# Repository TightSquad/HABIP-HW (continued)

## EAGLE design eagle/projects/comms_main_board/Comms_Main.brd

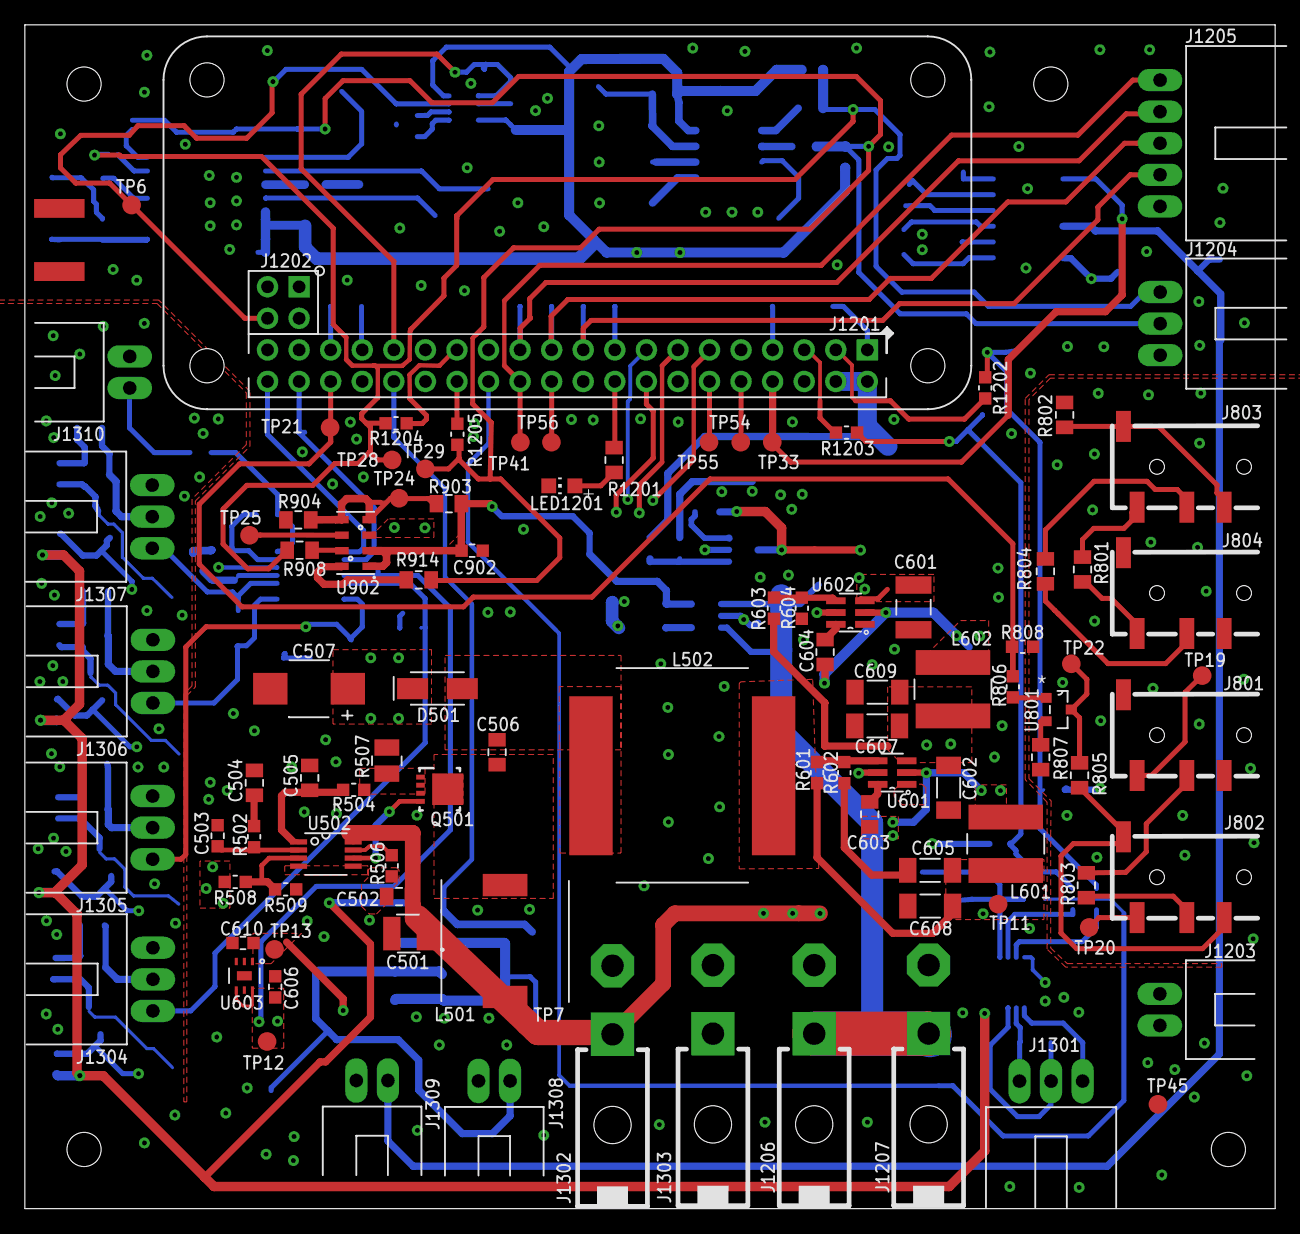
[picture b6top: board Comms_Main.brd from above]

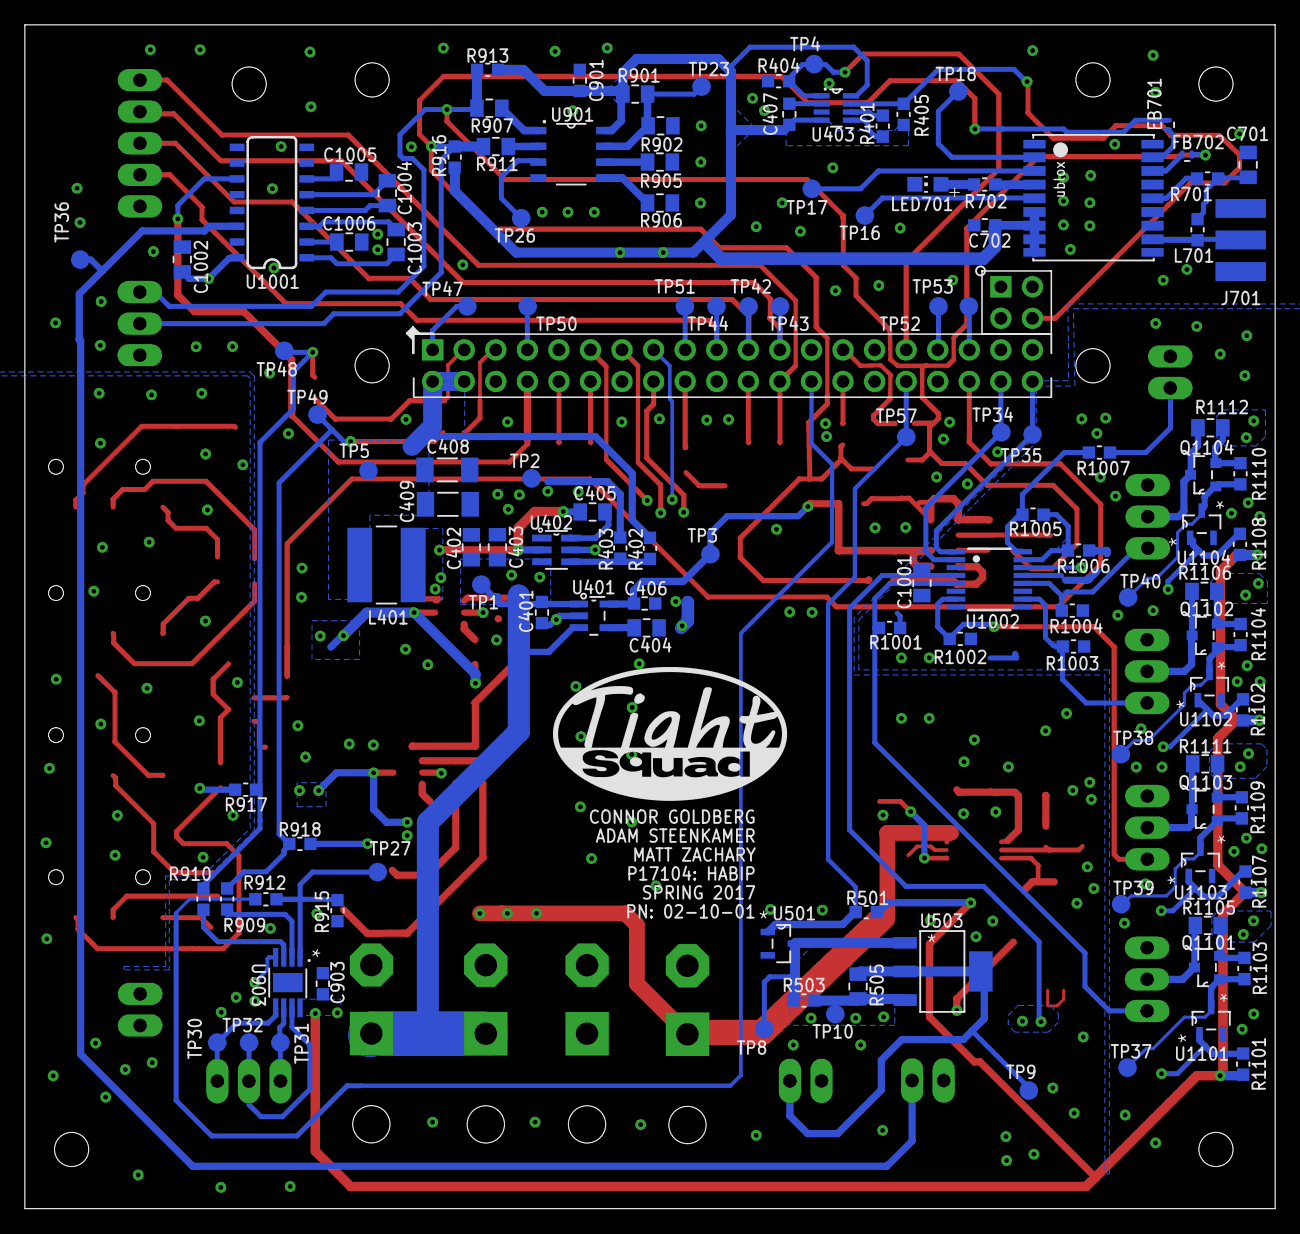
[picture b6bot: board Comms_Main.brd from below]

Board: 4 copper layers, 100.6 x 95.2 mm, 297 parts (122 on the bottom side), 126 nets.

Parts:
C401, C606, C610: 1uF; C0603
C402, C403: 10uF; C0805
C404, C701: 10nF; C0805
C405, C502, C504, C603, C604, C1001, C1002, C1003, C1004, C1005, C1006: 100nF; C0805
C406: 4.7uF; C0603
C407, C702, C901, C902, C903: 100nF; C0603
C408, C409, C602, C605, C607, C608, C609: 22uF; C1206
C501: 8.2 uF; C1411
C503: 2.4nF; C0603
C505: 620pF; C0805
C506: 4.7uF; C0805
C507: 47uF; C2917
C601: 22uF; C1210
D501: CDBA340-HF; DO-214AC
FB701, FB702: BLM15HD102SN1D; FB0402
H1201, H1202, H1203, H1204: MOUNT-HOLE_2.75; 2,75_HOLE_RASPI
IMAGE101: SQUAD_LOGO
J701: WRL-00593; SMA-EDGE
J801, J802, J803, J804: PRT-12639; AUDIO-JACK-TRRS-SMD
J1201: RECEPTACLE-2x20-254MM; HEADER-2X20-254MM
J1202: RECEPTACLE-2x2-254MM; HEADER-2X2-254MM
J1203, J1308, J1309, J1310: MOL-SL-2-RA; MOLSL-2-RA
J1204, J1301, J1304, J1305, J1306, J1307: MOL-SL-3-RA; MOLSL-3-RA
J1205: MOL-SL-5-RA; MOLSL-5-RA
J1206, J1207, J1302, J1303: MOL-MINIJR-2P-RA; 39-30-?02?
L401, L602: 4.7uH; SRN6045
L501: 10uH; SRU1048
L502: 68uH; HCMA1707
L601: 3.3uH; SRN6045
L701: 27nH; L0603
LED701, LED1201: LTST-C170CKT; CHIP-LED0805
OFFBOARD1, OFFBOARD7, OFFBOARD11, OFFBOARD30, OFFBOARD34, OFFBOARD38: 50-57-9403; MOLSL-OFFBOARD
OFFBOARD2, OFFBOARD4, OFFBOARD8, OFFBOARD10, OFFBOARD12, OFFBOARD14, OFFBOARD16, OFFBOARD17, OFFBOARD18, OFFBOARD19, OFFBOARD20, OFFBOARD21, OFFBOARD22, OFFBOARD23, OFFBOARD24, OFFBOARD25, OFFBOARD26, OFFBOARD27, OFFBOARD28, OFFBOARD29, OFFBOARD31, OFFBOARD32, OFFBOARD33, OFFBOARD35, OFFBOARD36, OFFBOARD37, OFFBOARD39, OFFBOARD40, OFFBOARD41, OFFBOARD43, OFFBOARD44: 0016020087; MOLSL-OFFBOARD
OFFBOARD3: 0050579405; MOLSL-OFFBOARD
OFFBOARD5: 67996-104HLF; MOLSL-OFFBOARD
OFFBOARD6: PRPC020DAAN-RC; MOLSL-OFFBOARD
OFFBOARD9, OFFBOARD13, OFFBOARD15, OFFBOARD42, OFFBOARD48: 50-57-9402; MOLSL-OFFBOARD
OFFBOARD45: 0701070001; MOLSL-OFFBOARD
OFFBOARD46, OFFBOARD47: 0016020115; MOLSL-OFFBOARD
OFFBOARD49, OFFBOARD52, OFFBOARD55, OFFBOARD56, OFFBOARD64, OFFBOARD65: 0039013022; MOLSL-OFFBOARD
OFFBOARD50, OFFBOARD51, OFFBOARD53, OFFBOARD54, OFFBOARD57, OFFBOARD58, OFFBOARD59, OFFBOARD60, OFFBOARD66, OFFBOARD67, OFFBOARD68, OFFBOARD69: 0039000073; MOLSL-OFFBOARD
OFFBOARD61, OFFBOARD70: 0039013023; MOLSL-OFFBOARD
OFFBOARD62, OFFBOARD63, OFFBOARD71, OFFBOARD72: 0039000075; MOLSL-OFFBOARD
OUTLINE1201: RASPI-ZERO-4STANDOFFS-0CAM; RASPI_ZERO_4STANDOFFS
Q501: CSD17579Q3A; DNH0008A
Q1101, Q1102, Q1103, Q1104: NTR4101PT1G; SOT103P240X110-3N
R401, R909, R910, R912, R915, R1005, R1006: 0; R0603
R402, R603: 56.2k; R0603
R403, R404, R405, R501, R503, R509, R602, R604, R1101, R1102, R1103, R1104, R1107, R1108, R1109, R1110: 10k; R0603
R502: 1.15k; R0603
R504: 100; R0603
R505, R801, R802, R803, R804, R805, R807, R901, R902, R903, R904, R905, R906, R907, R908, R911, R914, R1105, R1106, R1111, R1112: 0.0; R0805
R506: 30.1k; R0603
R507: 0.016; R1206
R508: 84.5k; R0603
R601: 33.2k; R0603
R701: 10; R0603
R702: 390; R0603
R806, R808: 1k; R0603
R913, R916, R917, R918: 4.7k; R0603
R1001, R1002, R1003, R1004, R1007: 75; R0603
R1201: 150; R0805
R1202, R1203, R1204, R1205: 23.2; R0603
TP1, TP2, TP3, TP4, TP5, TP6, TP7, TP8, TP9, TP10, TP11, TP12, TP13, TP16, TP17, TP18, TP19, TP20, TP21, TP22, TP23, TP24, TP25, TP26, TP27, TP28, TP29, TP30, TP31, TP32, TP33, TP34, TP35, TP36, TP37, TP38, TP39, TP40, TP41, TP42, TP43, TP44, TP45, TP47, TP48, TP49, TP50, TP51, TP52, TP53, TP54, TP55, TP56, TP57: TPTP15R; TP15R
U401: LP2985-33DBVR; DBV5
U402, U601, U602: TPS562209DDCT; DDC0006A
U403: MAX6371; SOT23P130X045-8N
U501, U1101, U1102, U1103, U1104: 2N7002P,215; SOT95P230X110-3N
U502: LM3488MMX/NOPB; MUA08A
U503: NDT2955; SOT230P700X180-4N
U603: LP5900SD-3.3/NOPB; 6WDFN
U701: MAX-M8Q; UBLOX_MAX
U801: MMBT3904-HF; SOT103P240X110-3N
U901: PCT2075D,118; SOIC127P130X0600-8N
U902: MS560702BA03-50; SMD125P110X060-8N
U903: MCP4541-103E/MS; SOP65P490X110-8N
U1001: MAX3232CSE+; SO016
U1002: MAX4311; QSOP16

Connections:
3P3V_DIG_POT: C605.1, C608.1, C903.1, L601.2, R501.2, R601.2, R917.2, R918.2, R1101.2, R1102.2, R1107.2, R1108.2, TP11.TP, U903.8
3P3V_RS232: C610.1, C1002.1, TP13.TP, U603.1, U1001.16
3P3V_SENSORS: C406.1, C407.1, C702.1, C901.2, C902.2, R401.1, R405.2, R901.2, R903.2, R913.2, R916.2, TP3.TP, U401.5, U403.4, U403.5, U403.8, U701.6_V_BCKP, U701.7_VCC_IO, U701.8_VCC, U701.9_V_RESET, U901.8, U902.1, U902.2
5V_BOARD: C602.1, C606.1, C607.1, C609.1, C1001.1, L602.2, Q1101.2, Q1102.2, Q1103.2, Q1104.2, R603.2, R1103.2, R1104.2, R1105.2, R1106.2, R1109.2, R1110.2, R1111.2, R1112.2, TP12.TP, U601.3, U601.5, U603.4, U603.6, U1002.4, U1002.14
5V_BUCK_SW: C604.2, L602.1, U602.2
5V_BUCK_VBST: C604.1, U602.6
5V_BUCK_VFB: R603.1, R604.2, U602.4
5V_CAM0: J1304.2, Q1101.3, R1105.1
5V_CAM1: J1305.2, Q1103.3, R1111.1
5V_CAM2: J1306.2, Q1102.3, R1106.1
5V_CAM3: J1307.2, Q1104.3, R1112.1
5V_PI: C408.1, C409.1, J1201.2, J1201.4, L401.2, R402.2, TP5.TP
7P4V_IN: C401.1, C402.1, C403.1, J1206.1, J1207.1, TP1.TP, U401.1, U401.3, U402.3, U402.5
11P1V_IN: C501.1, C502.1, C601.1, J1302.1, L501.1, TP7.TP, U502.8, U602.3, U602.5
12V_BOARD: C507.1, D501.C, J1303.1, R503.2, R505.2, R508.2, TP10.TP, U503.3
12V_PI_CONTROLLED: J1308.1, R505.1, TP9.TP, U503.2, U503.4
12V_PMOS_G: R503.1, TP8.TP, U501.3, U503.1
BUCK_POT_SW: C603.2, L601.1, U601.2
BUCK_POT_VBST: C603.1, U601.6
BUCK_POT_VFB: R601.1, R602.2, U601.4
CAM0_P_G: Q1101.1, R1103.1, TP37.TP, U1101.3
CAM1_P_G: Q1103.1, R1109.1, TP39.TP, U1103.3
CAM2_P_G: Q1102.1, R1104.1, TP38.TP, U1102.3
CAM3_P_G: Q1104.1, R1110.1, TP40.TP, U1104.3
DCDC_STEPUP_COMP: C503.1, R502.2, U502.2
DCDC_STEPUP_DR: Q501.4, U502.6
DCDC_STEPUP_FB: R508.1, R509.2, U502.3
DCDC_STEPUP_ISENSE: C505.1, R504.1, U502.1
DCDC_STEPUP_ISENSE_RES: Q501.1, Q501.2, Q501.3, R504.2, R507.2
DCDC_STEPUP_OUT: C506.1, L501.2, Q501.5, Q501.6, Q501.7, Q501.8, Q501.9, Q501.V
DCDC_STEPUP_PRE_DIODE: C506.2, D501.A, L502.1
DCDC_STEPUP_RC_COMP: C504.1, R502.1
DCDC_STEPUP_SD: R506.2, U502.7
GND: C401.2, C402.2, C403.2, C404.2, C406.2, C407.2, C408.2, C409.2, C501.2, C502.2, C503.2, C504.2, C505.2, C507.2, C601.2, C602.2, C605.2, C606.2, C607.2, C608.2, C609.2, C610.2, C701.2, C702.2, C901.1, C902.1, C903.2, C1001.2, C1002.2, C1005.2, C1006.2, J701.GND@0, J701.GND@1, J701.GND@2, J701.GND@3, J801.EARTH, J801.RING2, J804.EARTH, J804.RING2, J1201.6, J1201.9, J1201.14, J1201.20, J1201.25, J1201.30, J1201.34, J1201.39, J1202.2, J1203.1, J1203.2, J1204.3, J1205.5, J1206.2, J1207.2, J1302.2, J1303.2, J1304.3, J1305.3, J1306.3, J1307.3, J1308.2, J1309.2, J1310.2, L502.2, LED701.C, LED1201.C, R403.1, R404.1, R506.1, R507.1, R509.1, R602.1, R604.1, R802.1, R807.2, R808.2, R902.1, R904.1, R905.1, R906.1, R915.1, R1001.1, R1002.1, R1003.1, R1004.1, R1006.1, TP2.TP, TP45.TP, U401.2, U402.1, U403.2, U501.2, U502.4, U502.5, U601.1, U602.1, U603.3, U603.7, U701.1_GND, U701.10_GND, U701.12_GND, U901.4, U902.3, U903.4, U1001.8, U1001.10, U1001.13, U1001.15, U1002.13, U1101.2, U1102.2, U1103.2, U1104.2
GPIO_MUX_ADDR0: J1201.38, TP34.TP, U1002.2
GPIO_MUX_ADDR1: J1201.40, TP35.TP, U1002.1
GPIO_POT_HVC: J1201.26, R912.1
GPIO_PTT: J1201.36, R806.1, R808.1, TP21.TP
GPS_ANTENNA: J701.SIG, L701.1, U701.11_RF_IN
GPS_EXTINT: TP16.TP, U701.5_EXTINT0
GPS_LED_DRIVE: LED701.A, R702.2
GPS_RXD: TP17.TP, U701.3_RXD1
GPS_SCL: FB701.2, U701.17_SCL2
GPS_SDA: FB702.2, U701.16_SDA2
GPS_TIMEPULSE: R702.1, U701.4_TIMEPULSE
GPS_TXD: TP18.TP, U701.2_TXD1
GPS_VCC-RF: R701.2, U701.14_VCC_RF
GPS_VCC_RF_RLC: C701.1, L701.2, R701.1
MISO: J1201.21, J1205.3, TP42.TP
MOSI: J1201.19, J1205.4, TP44.TP
MUX_FB: R1005.1, R1006.2, U1002.15
MUX_OUT: R1005.2, R1007.2, U1002.16
OSD_DATA: J1309.1, TP36.TP, U1001.14
PI_3P3V: J1201.1, TP47.TP
PI_3P3V_2: J1201.17, TP51.TP
PI_12V_CTL: J1201.32, R501.1, TP57.TP, U501.1
PI_BUCK_SW: C405.2, L401.1, U402.2
PI_BUCK_VBST: C405.1, U402.6
PI_BUCK_VFB: R402.1, R403.2, U402.4
PI_CAM0_VCTL: J1201.11, R1101.1, U1101.1
PI_CAM1_VCTL: J1201.13, R1107.1, U1103.1
PI_CAM2_VCTL: J1201.15, R1102.1, U1102.1
PI_CAM3_VCTL: J1201.16, R1108.1, U1104.1
PI_GPCLK0: J1201.7, TP50.TP
PI_GPIO25: J1201.22, TP56.TP
PI_LED_DRIVE: LED1201.A, R1201.2
PI_MISO1: J1201.35, TP53.TP
PI_PWM0: J1201.12, TP55.TP
PI_PWM1: J1201.33, TP52.TP
PI_SCL: J1201.28, R1205.1
PI_SCL_5: J1201.5, R1203.2
PI_SDA: J1201.27, R1204.2
PI_SDA_3: J1201.3, R1202.2
PI_STATUS_LED: J1201.18, R1201.1
PI_UART_RXD: J1201.10, TP54.TP
POT_A: J1301.1, TP30.TP, U903.5
POT_B: J1301.2, TP32.TP, U903.7
POT_HVCA0: R912.2, R915.2, TP27.TP, U903.1
POT_SCL: R909.1, R918.1, R1203.1, TP49.TP
POT_SCL_IN: R909.2, U903.2
POT_SDA: R910.1, R917.1, R1202.1, TP48.TP
POT_SDA_IN: R910.2, U903.3
POT_W: J1301.3, TP31.TP, U903.6
PRES_CSB: R903.1, R904.2, TP24.TP, U902.4, U902.5
PRES_SCL: R914.1, U902.8
PRES_SDA: R908.1, U902.7
PRES_SDO: TP25.TP, U902.6
PTT: R805.1, TP22.TP, U801.3
PTT_BJT_B: R806.2, U801.1
PTT_BJT_E: R807.1, U801.2
RS232_C1+: C1003.1, U1001.1
RS232_C1-: C1003.2, U1001.3
RS232_C2+: C1004.1, U1001.4
RS232_C2-: C1004.2, U1001.5
RS232_V+: C1006.1, U1001.2
RS232_V-: C1005.1, U1001.6
RX_IN_R: J804.RING1, R804.1
RX_IN_T: J804.TIP, R801.1
RX_OUT_R: J803.RING1, R804.2
RX_OUT_S: J803.EARTH, J803.RING2, R802.2
RX_OUT_T: J803.TIP, R801.2
SCL: FB701.1, J1204.2, R911.2, R914.2, R916.1, R1205.2, TP29.TP
SCLK: J1201.23, J1205.2, TP43.TP
SDA: FB702.1, J1204.1, R907.2, R908.2, R913.1, R1204.1, TP28.TP
SENSOR_LDO_BYPASS: C404.1, U401.4
SS: J1201.24, J1205.1, TP41.TP
TEMP_A0: R901.1, R902.2, TP23.TP, U901.7
TEMP_A1: R905.2, U901.6
TEMP_A2: R906.2, U901.5
TEMP_OS: TP26.TP, U901.3
TEMP_SCL: R911.1, U901.2
TEMP_SDA: R907.1, U901.1
TX_IN_R: J801.RING1, R803.2
TX_IN_T: J801.TIP, TP19.TP
TX_OUT_R: J802.RING1, R803.1
TX_OUT_S: J802.EARTH, J802.RING2, R805.2
TX_OUT_T: J802.TIP, TP20.TP
UART_TXD: J1201.8, TP33.TP, U1001.11
VID_IN0: J1304.1, R1001.2, U1002.5
VID_IN1: J1305.1, R1002.2, U1002.7
VID_IN2: J1306.1, R1003.2, U1002.10
VID_IN3: J1307.1, R1004.2, U1002.12
VID_OUT: J1310.1, R1007.1
WDT_BITE_N: J1202.4, R405.1, TP6.TP, U403.7
WDT_PET: J1201.31, R404.2, TP4.TP, U403.1
WDT_SET2: R401.2, U403.6

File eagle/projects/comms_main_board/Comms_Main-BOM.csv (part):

"Qty"	"Value"	"Device"	"Parts"	"BOM"	"CAP_REV_V"	"CURRENT_AVG_RECT"	"CURRENT_DC"	"CURRENT_REV_LEAK"	"CURRENT_SAT"	"DCR_MAX"	"ESR"	"FINISH"	"FORWARD_CURRENT"	"FORWARD_VOLTAGE"	"IMPEDANCE"	"INTERFACE"	"LOCKING"	"MANUFACTURER"	"MANUFACTURER_PN"	"MAX_CURRENT"	"MOUNT_ANGLE"	"MOUNT_TYPE"	"MPN"	"OC_FARNELL"	"OC_NEWARK"	"OUTPUT_ACTIVE"	"OUTPUT_ACTIVE_TIME"	"OUTPUT_BITS"	"OUTPUT_TYPE"	"PACKAGE"	"PITCH"	"POSITIONS"	"POWER"	"PRESSURE_TYPE"	"RESOLUTION"	"ROWS"	"SHIELDED"	"STARTUP_DELAY"	"TEMP_COEFF"	"TIMEOUT"	"TOLERANCE"	"TP_SIGNAL_NAME"	"TYPE"	"VALUE"	"VENDOR"	"VENDOR_PN"	"VOLTAGE"	"VOLTAGE_DC_REV"	"VOLTAGE_FWD"
"3"	"1uF"	"CAP_1UF0_0603"	"C401, C606, C610"	""	""	""	""	""	""	""	""	""	""	""	""	""	""	"Murata"	"GRM188R61C105KA93D"	""	""	""	""	""	""	""	""	""	""	""	""	""	""	""	""	""	""	""	"X5R"	""	"10%"	""	""	"1uF"	"Digi-Key"	"490-1536-1-ND"	"16V"	""	""
"2"	"10uF"	"CAP_10UF0_0805"	"C402, C403"	""	""	""	""	""	""	""	""	""	""	""	""	""	""	"Murata Electronics North America"	"GRM21BR61C106KE15L"	""	""	""	""	""	""	""	""	""	""	""	""	""	""	""	""	""	""	""	"X5R"	""	"10%"	""	""	"10uF"	"Digi-Key"	"490-3886-1-ND"	"16V"	""	""
"2"	"10nF"	"CAP_10NF0_0805"	"C404, C701"	""	""	""	""	""	""	""	""	""	""	""	""	""	""	"Kemet"	"C0805C103K5RACTU"	""	""	""	""	""	""	""	""	""	""	""	""	""	""	""	""	""	""	""	"X7R"	""	"10%"	""	""	"10nF"	"Digi-Key"	"399-1158-1-ND"	"50V"	""	""
"11"	"100nF"	"CAP_100NF0_0805"	"C405, C502, C504, C603, C604, C1001, C1002, C1003, C1004, C1005, C1006"	""	""	""	""	""	""	""	""	""	""	""	""	""	""	"AVX Corporation"	"08053C104KAT2A"	""	""	""	""	""	""	""	""	""	""	""	""	""	""	""	""	""	""	""	"X7R"	""	"10%"	""	""	"100nF"	"Digi-Key"	"478-3755-1-ND"	"25V"	""	""
"1"	"4.7uF"	"CAP_4UF7_0603"	"C406"	""	""	""	""	""	""	""	""	""	""	""	""	""	""	"Murata"	"GRM188R60J475KE19D"	""	""	""	""	""	""	""	""	""	""	""	""	""	""	""	""	""	""	""	"X5R"	""	"10%"	""	""	"4.7uF"	"Digi-key"	"490-3297-1-ND"	"6.3V"	""	""
"5"	"100nF"	"CAP_100NF0_0603"	"C407, C702, C901, C902, C903"	""	""	""	""	""	""	""	""	""	""	""	""	""	""	"Murata"	"GRM188R71C104KA01D"	""	""	""	""	""	""	""	""	""	""	""	""	""	""	""	""	""	""	""	"X7R"	""	"10%"	""	""	"100nF"	"Digi-key"	"490-1532-1-ND"	"16V"	""	""
"7"	"22uF"	"CAP_22UF0_1206"	"C408, C409, C602, C605, C607, C608, C609"	""	""	""	""	""	""	""	""	""	""	""	""	""	""	"Murata Electronics North America"	"GRM31CR61A226ME19L"	""	""	""	""	""	""	""	""	""	""	""	""	""	""	""	""	""	""	""	"X5R"	""	"20%"	""	""	"22uF"	"Digi-Key"	"490-4738-1-ND"	"10V"	""	""
"1"	"8.2 uF"	"CAP_POL_8UF2_1411"	"C501"	""	""	""	""	""	""	""	"100 mOhm"	""	""	""	""	""	""	"Panasonic"	"20TQC8R2M"	""	""	""	""	""	""	""	""	""	""	""	""	""	""	""	""	""	""	""	""	""	"20%"	""	""	"8.2 uF"	"Digi-Key"	"P16504CT-ND"	"20V"	""	""
"1"	"2.4nF"	"CAP_2NF4_0603"	"C503"	""	""	""	""	""	""	""	""	""	""	""	""	""	""	"Murata"	"GRM1885C1H242JA01D"	""	""	""	""	""	""	""	""	""	""	""	""	""	""	""	""	""	""	""	"C0G, NP0"	""	"5%"	""	""	"2.4nF"	"Digi-Key"	"490-3282-1-ND"	"50V"	""	""
"1"	"620pF"	"CAP_620PF0_0805"	"C505"	""	""	""	""	""	""	""	""	""	""	""	""	""	""	"Samsung Electro-Mechanics America, Inc."	"CL21C621JBCNNNC"	""	""	""	""	""	""	""	""	""	""	""	""	""	""	""	""	""	""	""	"C0G, NP0"	""	"5%"	""	""	"620pF"	"Digi-Key"	"1276-2677-1-ND"	"50V"	""	""
"1"	"4.7uF"	"CAP_4UF7_0805"	"C506"	""	""	""	""	""	""	""	""	""	""	""	""	""	""	"Murata"	"GRM21BR61E475MA12L"	""	""	""	""	""	""	""	""	""	""	""	""	""	""	""	""	""	""	""	"X5R"	""	"20%"	""	""	"4.7uF"	"Digi-Key"	"490-5422-1-ND"	"25V"	""	""
"1"	"47uF"	"CAP_POL_47UF0_2917"	"C507"	""	""	""	""	""	""	""	"30mOhm"	""	""	""	""	""	""	"KEMET"	"T521X476M035ATE030"	""	""	""	""	""	""	""	""	""	""	""	""	""	""	""	""	""	""	""	""	""	"20%"	""	""	"47uF"	"Digi-Key"	"399-5937-1-ND"	"35V"	""	""
"1"	"22uF"	"CAP_22UF0_1210"	"C601"	""	""	""	""	""	""	""	""	""	""	""	""	""	""	"Murata"	"GRM32ER61E226KE15L"	""	""	""	""	""	""	""	""	""	""	""	""	""	""	""	""	""	""	""	"X5R"	""	"10%"	""	""	"22uF"	"Digi-key"	"490-3889-1-ND"	"25V"	""	""
"1"	"CDBA340-HF"	"DIODE-SCHOTTKY_DO-214AC"	"D501"	""	"200pF @4V, 1MHz"	"3A"	""	"500uA @40V"	""	""	""	""	""	""	""	""	""	"Comchip"	"CDBA340-HF"	""	""	""	""	""	""	""	""	""	""	""	""	""	""	""	""	""	""	""	""	""	""	""	""	"CDBA340-HF"	"Digi-key"	"641-1748-1-ND"	""	"40V"	"500mV @3A"
"2"	"BLM15HD102SN1D"	"FERRITE_BEAD-0402"	"FB701, FB702"	""	""	""	""	""	""	"1.25 Ohm"	""	""	""	""	"1kOhm @100MHz"	""	""	"Murata"	"BLM15HD102SN1D"	"250mA"	""	""	""	""	""	""	""	""	""	""	""	""	""	""	""	""	""	""	""	""	""	""	""	"BLM15HD102SN1D"	"Digi-Key"	"490-4003-1-ND"	""	""	""
"4"	"MOUNT-HOLE_2.75"	"MOUNT-HOLE_2.75"	"H1201, H1202, H1203, H1204"	""	""	""	""	""	""	""	""	""	""	""	""	""	""	""	""	""	""	""	""	""	""	""	""	""	""	""	""	""	""	""	""	""	""	""	""	""	""	""	""	""	""	""	""	""	""
"1"	"SQUAD_LOGO"	"SQUAD_LOGO"	"IMAGE101"	""	""	""	""	""	""	""	""	""	""	""	""	""	""	""	""	""	""	""	""	""	""	""	""	""	""	""	""	""	""	""	""	""	""	""	""	""	""	""	""	""	""	""	""	""	""
"1"	"WRL-00593"	"SMA_EDGE"	"J701"	""	""	""	""	""	""	""	""	""	""	""	""	""	""	"Sparkfun"	"WRL-00593"	""	""	""	""	""	""	""	""	""	""	""	""	""	""	""	""	""	""	""	""	""	""	""	""	"WRL-00593"	"Sparkfun"	"WRL-00593"	""	""	""
"4"	"PRT-12639"	"PRT-12639"	"J801, J802, J803, J804"	""	""	""	""	""	""	""	""	""	""	""	""	""	""	"Sparkfun"	"PRT-12639"	""	""	""	""	""	""	""	""	""	""	""	""	""	""	""	""	""	""	""	""	""	""	""	""	"PRT-12639"	"SPARKFUN"	"PRT-12639"	""	""	""
"1"	"RECEPTACLE-2x20-254MM"	"RECEPTACLE-2X20-254MM"	"J1201"	""	""	""	""	""	""	""	""	"Gold"	""	""	""	""	""	"Sullins Connector Solutions"	"SFH11-PBPC-D20-ST-BK"	"3A"	"Vertical"	"TH"	""	""	""	""	""	""	""	""	"2.54mm"	"40"	""	""	""	"2"	""	""	""	""	""	""	""	"RECEPTACLE-2x20-254MM"	"Digi-Key"	"S9200-ND"	""	""	""
"1"	"RECEPTACLE-2x2-254MM"	"RECEPTACLE-2X2-254MM"	"J1202"	""	""	""	""	""	""	""	""	"Gold"	""	""	""	""	""	"Sullins Connector Solutions"	"PPPC022LFBN-RC"	"3A"	"Vertical"	"TH"	""	""	""	""	""	""	""	""	"2.54mm"	"4"	""	""	""	"2"	""	""	""	""	""	""	""	"RECEPTACLE-2x2-254MM"	"Digi-Key"	"S7105-ND"	""	""	""
"4"	"MOL-SL-2-RA"	"MOLSL_2PIN_SL2RA_RA"	"J1203, J1308, J1309, J1310"	""	""	""	""	""	""	""	""	"GOLD"	""	""	""	""	"YES"	"Molex"	"0705530001"	"3.0A"	"RIGHT"	"TH"	""	""	""	""	""	""	""	""	""	"2"	""	""	""	""	""	""	""	""	""	""	""	"MOL-SL-2-RA"	"Digi-key"	"WM4900-ND"	""	""	""
"6"	"MOL-SL-3-RA"	"MOLSL_3PIN_SL3RA_RA"	"J1204, J1301, J1304, J1305, J1306, J1307"	""	""	""	""	""	""	""	""	"GOLD"	""	""	""	""	"YES"	"Molex"	"0705530002"	"3.0A"	"RIGHT"	"TH"	""	""	""	""	""	""	""	""	""	"3"	""	""	""	""	""	""	""	""	""	""	""	"MOL-SL-3-RA"	"Digi-key"	"WM4901-ND"	""	""	""
"1"	"MOL-SL-5-RA"	"MOLSL_5PIN_SL4RA_RA"	"J1205"	""	""	""	""	""	""	""	""	"GOLD"	""	""	""	""	"YES"	"Molex"	"0705530004"	"3.0A"	"RIGHT"	"TH"	""	""	""	""	""	""	""	""	""	"5"	""	""	""	""	""	""	""	""	""	""	""	"MOL-SL-5-RA"	"Digi-key"	"WM4903-ND"	""	""	""
"4"	"MOL-MINIJR-2P-RA"	"39-30-02?"	"J1206, J1207, J1302, J1303"	""	""	""	""	""	""	""	""	"GOLD"	""	""	""	""	"YES"	"Molex"	"0039301021"	"13.0A"	"RIGHT"	"TH"	""	""	""	""	""	""	""	""	""	"2"	""	""	""	""	""	""	""	""	""	""	""	"MOL-MINIJR-2P-RA"	"Digi-Key"	"WM1363-ND"	""	""	""
"2"	"4.7uH"	"L_4UH7"	"L401, L602"	""	""	""	"3A"	""	"4A"	"37.6mOHM"	""	""	""	""	""	""	""	"Bourns Inc."	"SRN6045-4R7Y"	""	""	""	""	""	""	""	""	""	""	""	""	""	""	""	""	""	"Yes"	""	""	""	"30%"	""	"Wirewound"	"4.7uH"	"Digi-Key"	"SRN6045-4R7YCT-ND"	""	""	""
"1"	"10uH"	"L_10UH0-"	"L501"	""	""	""	"4.5A"	""	"3.7A"	"18.5mOHM"	""	""	""	""	""	""	""	"Bourns Inc"	"SRU1048-100Y"	""	""	""	""	""	""	""	""	""	""	""	""	""	""	""	""	""	"Yes"	""	""	""	"30%"	""	"Wirewound"	"10uH"	"Digi-key"	"SRU1048-100YCT-ND"	""	""	""
"1"	"68uH"	"L_68UH0-680-R"	"L502"	""	""	""	"5.2A"	""	"6.5A"	"85 mOhm"	""	""	""	""	""	""	""	"Eaton"	"HCMA1707-680-R"	""	""	""	""	""	""	""	""	""	""	""	""	""	""	""	""	""	"Yes"	""	""	""	"20%"	""	"Wirewound"	"68uH"	"Digi-Key"	"283-4574-1-ND"	""	""	""
"1"	"3.3uH"	"L_3UH3"	"L601"	""	""	""	"3.2A"	""	"5A"	"30.2mOHM"	""	""	""	""	""	""	""	"Bourns Inc."	"SRN6045-3R3Y"	""	""	""	""	""	""	""	""	""	""	""	""	""	""	""	""	""	"Yes"	""	""	""	"30%"	""	"Wirewound"	"3.3uH"	"Digi-Key"	"SRN6045-3R3YCT-ND"	""	""	""
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
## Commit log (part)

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2016-12-06 Added inductor to power management and added new common library of passive and random parts
2016-12-07 GRSS foundation built
2016-12-07 Swapped i2c pull up resistor location
2016-12-07 added all pi hat schematic elements
2016-12-07 Fixing DRCs, so we can start a PCB layout
2016-12-07 moved cap / res 0603 from other libraries to GRSS Lib
2016-12-07 added mounting for for Raspi
2016-12-07 Add blank PCB
2016-12-07 Added 9V value to 9V battery connector
2016-12-07 Changed ignore file to ignore pdfs
2016-12-07 Added pin to NC symbol
2016-12-07 Updated daqcs_host library parts attributes
2016-12-07 Fixed part number on an inductor
2016-12-07 Added 10pF to GRSS Cap Lib
2016-12-07 Updates to library parts and schematic
2016-12-07 Added a 2pin header to GRSS Lib
2016-12-08 GRSS gooooooood for DDR for now
2016-12-08 adding BOMs
2016-12-08 Updated Libraries thingys, not sure, probably broke it
2016-12-11 modified cap and res to have more attributes
2016-12-12 added molex SL connectors to daqcs_host library
2016-12-13 added SL 3-pin connector. Right-angle tPlace/tDocu has not been edited
2016-12-13 added SL 5-pin connector. Right-angle tPlace/tDocu has not been edited
2016-12-13 modified pi hat schematic. Added second temp sensor. Removed Honeywell pressure sensor for two TE sensors
2017-01-06 Added mounting holes to DAQCS Host Board
2017-01-17 added 3.3V LDO for non- RasPi operation
2017-01-18 added WDT and reset MUX to the schematic. STILL NEED TO CONNECT WDT INPUTS TO THE RASPI. I will add two more pins from the Pi to cover this. More TO DO: add humidity sensor, update block diagram page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
2017-01-18 Added SL connectors to COMMS library
2017-01-18 removed USB connector since it is not 100% needed. It was a nice to have that can go. I also removed the GPIO pin to selectively disable the WDT. This, again, is a nice to have but not needed since t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
2017-01-19 added Humidity sensor. Still need to add camera mounting holes, recheck schematic, and the update the block diagram.
2017-01-19 Modified the gitignore file to allow PDFs. added all datasheet PDF files
2017-01-19 Fixed MAX4311 footprint
2017-01-19 adding pin header data sheets
2017-01-19 added inverting OD buffer so that the MSP can drive the RUN pin on the Pi. This allows the MSP to either cycle all RasPi power or just hard reset the BCM (note this is done through a stuff option, ca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
2017-01-19 corrected mounting holes for RasPi and Cam. added the correct holes to the schematic. TO DO: make a template part that has the correct HAT outline and mounting holes for the external 3 standoffs
2017-01-20 Fixed spacing on digi pot part footprint
2017-01-21 Trying to import image as schematic symbol
2017-01-22 Switched some DAQCS parts to COMMS parts (libraries). Added test points to power management section. Added connector for antenna ground
2017-01-23 COMMS block diagram images for schematic
2017-01-24 renamed file name for Honey sensor... for steve
2017-01-24 Added battery sense circuits
2017-01-24 added ne PP3V3_HAT rail so that the one from the Pi can be disconnected if needed
2017-01-24 Added power to balloon pressure sensor connector
2017-01-24 adding datasheet for new inductor and IMU
2017-01-24 Added 7pin Molex SL connectors
2017-01-24 Changed GPS LED resistor. Added parameters to schematics for resistors, inductors, capacitors. Named nets on schematics
2017-01-25 Added status LEDs to MSP430s names to all nets
2017-01-25 added IMU footprint and device
2017-01-25 fixed outline and pin 1 location of IMU
2017-01-25 removed an unused part from GRSS lib
2017-01-25 fixed Power FET symbol on weird grid
2017-01-25 switched from KK to SL connectors
2017-01-25 TOC / Title Page for GRSS
2017-01-25 Updated GRSS component symbols for aestetics / info
2017-01-25 ERC check quick
2017-01-25 rando
2017-01-26 Updated Battery Holder Package with Name / Value
2017-01-26 Added Test Point to lib
2017-01-26 Added additional IMU with I2C interface
2017-01-26 schematic finalized. To Do: (1) component checks for symbol/pinout/footprint (2) check all passive component ratings (3) check all LEDs (4) check charger connector power FET (5) edit block diagram
2017-01-26 Added block diagram page
2017-01-26 Package updates for component check / added block diagram sheet
2017-01-26 fixed some ERC errors and warnings
2017-01-26 Fixed 12V boost power section of COMMS board. Finished creating parts for it in library.
2017-01-27 grouped all components in layout
2017-01-27 modified IMU footprint for minimum .13mm spacing between pads
2017-01-27 Fixed 47uH inductor footprint. Fixed a few simple ERC errors
2017-01-27 Fixed manufacturer part number value for some parts
2017-01-28 Added headers for both MSP430s to pin out the additonal GPIO
2017-01-29 modified HAT block diagram. schematic looks good to go
2017-01-29 added POR variant for sensor HAT
2017-01-30 added all connector assembly parts and external sensors to the schematic. they will now appear in the BOM! The only parts that will not appear there now are the Battery and the standoffs
2017-01-30 GRSS board placement concept
2017-01-30 board update rq
2017-01-31 Update COMMS schematic pdf
2017-01-31 Component placement sonnn
2017-01-31 Update NPN BJT digikey numbers
2017-01-31 Added a NMOS and PMOS for OSD Power Circuit
2017-01-31 added new parts for TPS61253 converter, which will replace the TPS61089
2017-02-01 added new Boost regulator, which has true shutdown
2017-02-01 Continued part placement
2017-02-01 Begin layout
2017-02-01 Layout of audio cables
2017-02-01 PNP pads
2017-02-01 Small changes to schematic
2017-02-01 added mounting holes to lib / sch
2017-02-01 Fixed MSP430 package layers and added brd file
2017-02-01 modified block diagram for final circuit
2017-02-01 Fixed all schematic ERCs except for IMU and Humidity sensor. Changed all power line jumpers to 0805
2017-02-01 LDO updated
2017-02-01 Changed WDT to be off 3.3V rail
2017-02-02 swapped battery charger for AC variant. Checked charger symbol and footprint :)
2017-02-02 Update inductor
2017-02-03 Changed motor battery Vsense
2017-02-03 routing gps module
2017-02-03 Added parameters to an inductor part
2017-02-03 removed zeners
2017-02-04 Updated Resistors to be 0805 and added 3 0805 res to Lib
2017-02-04 battery holder pn update
2017-02-05 Added optocoupler isolation for cutdown mechanism
2017-02-05 checked schematic pages 1,2,3 including symbols and footprints. Check all resistor, LED, and capacitor components
2017-02-06 Small change
2017-02-07 Started power layout
2017-02-07 Added EAGLE design rules
2017-02-07 Updated part nums
2017-02-07 Work on the power management placement and routing. Also added new schematic pdfs
2017-02-07 Added 0.01uF 0805 to lib
2017-02-07 Swap LDO U603 for DFN package, vs BGA
2017-02-07 Major routing done
2017-02-08 Updated design rules
2017-02-08 checked Adam's dru. looks good. modified the description
2017-02-08 more placement
2017-02-08 modified RA SL connectors for proper width and height on the board. they can now be abutted by silk screen for close spacing. takes into account tolerances. modified pad annular ring in DRCs to 14mils
2017-02-08 lots of placement and routing
2017-02-09 Updated tdocu and tsilk layers of SL connectors used in COMMS board.
2017-02-09 TP on GND
2017-02-09 a lot more placement. Getting there
2017-02-09 finifhed placement. need to double check
2017-02-09 Worked on power layout and tracing to msp430s
2017-02-10 moving along with placement check and routing.
2017-02-10 Worked on cutdown routing and placement
2017-02-10 almost done with routing. Move the ADC to north side to allow for I2C clip TPs
2017-02-10 Updating placement and routing for sensors
2017-02-10 rough initial placement... 66x50mm
2017-02-11 more routing and power planing. move the I2C series resisters after the nostuff pullups. Needed to do this because I placed them under a connector :)
2017-02-11 Modified IMU2 interrupt pinout
2017-02-11 placing testpoints
2017-02-11 Fixed DRCs, cleaned up board
2017-02-12 Cleaned up bottom layer, fixed DRCs
2017-02-12 Updated LED series resistor to 200 ohms
2017-02-12 small placement change
2017-02-13 fixed up poly isolation. changed all traces to 10mil width except for current sense on the TOP and IMU trace on the bottom
2017-02-13 changed board outline to be added only on the board. modified the Raspi outline schematic symbol to only include the mouting holes
2017-02-13 modified DRU file for 2.5mil solder mask swell instead of 4mil
2017-02-13 modified RA SL connector silk to move away from the pads sm expansion
2017-02-13 updated all top and bottom silk
2017-02-13 Made fonts vectorized
2017-02-13 Finished routing al necessary connectons
2017-02-14 Attempt at LDO / 555 Timer solo Layout
2017-02-14 modified DRC for board thickness. added CAM directory and 4layer CAM script
2017-02-14 LG Route Take 1
2017-02-14 Connectors now not hanging off sides, now 62x66mm2
2017-02-14 Fixed some tNames
2017-02-14 Fix DRCs, unrouted nets
2017-02-14 Fixed DRCs in parts
2017-02-14 updated FET, LDO, 555 Timer for dots / silkscreen
2017-02-14 Fixed value placement on comms board
2017-02-14 Fix all DRCs, pour ground and power
2017-02-14 Added Squad Logo
2017-02-14 Board thermals
2017-02-14 tweaking power planes
2017-02-14 Reverted silly mistake
2017-02-14 Modified TOC and part numbers after a schematic page was added by Connor for NTSC camera power control
2017-02-15 Routed everything except Camera power controls, fixed DRCs
2017-02-15 Routed additional camera power control lines
2017-02-15 Fixed all DRC errors and updated silkscreens
2017-02-16 Squad Logo / 2-layer
2017-02-16 GND / Power Planes - LG
2017-02-16 Added logo and updating trace widths
2017-02-17 Separate ground planes for Audio and Video mux
2017-02-18 Finished making traces larger
2017-02-20 moved mounting holes briefly
2017-02-20 Added pull down to PTT line
2017-02-20 Made some changes to errors in cutdown mechanism
2017-02-21 added tyrap holes / updated silkscreen of battery
2017-02-22 small layout updates
2017-02-22 Separated i2c lines for Dig Pot
2017-02-22 Added off-board connectors, housing, crimps to schematic so they show up in the BOM (for comms board).
2017-02-22 Added damping resistors to comms board i2c pins
2017-02-23 Created latest comms board BOM
2017-02-24 Added text, fixed ground shorts, fixed text sizes
2017-02-24 Added current BOM
2017-02-25 added balloon sensor board
2017-02-26 somehow PP3V3_HAT got renamed to NFO???
2017-02-27 Layout changes per Adams review
2017-02-27 Fixed some text overlapping mask
2017-02-27 cleaned up HAT and balloon_sensor for panelling
2017-02-27 Added P/N to Board
2017-02-27 added panels
2017-02-27 GRSS now 62 height, 65 width
2017-02-27 made height of board 100mm
2017-02-27 modified CAM milling. added gerbmerge
2017-02-28 Fixed small issue with battery pack being completly wrong
2017-02-28 modified HAT and balloon_sensor to have layer 117 for board outline. adding all files for gerbmerge since it is now working. config file needed 5 for number of decimal places in drill file
2017-02-28 470k to 100k for better 555 timer period
2017-02-28 Fixed a ground via
2017-02-28 gerber
2017-02-28 zip for gerber for online viewer
2017-02-28 Redid group connections
2017-02-28 Added merged comms board gerbers for the panel
2017-02-28 Small fixes to power packages and power fet layout
2017-02-28 Fixed the power mosfet mixup
2017-03-01 Changed the power fet symbol and attached the powerpad on the 5V boost to ground pour
2017-03-01 adding some app notes
2017-03-01 added hat and balloon sensor gerbers for panel
2017-03-01 Removed a large trace on power plane, updated some silkscreen
2017-03-01 added modified BOMs to remove non-component parts, samples, and column for a board instance multiplier
2017-03-01 Added rev1 folder with gerbers and bom
2017-03-01 Added bom-in-line items to sch / lib and outputted fresh sch
2017-03-01 moved rev1 gerber
2017-03-01 rotated GRSS in the grss hat host panel
2017-03-01 adding camera cable adapter board
2017-03-02 added panel DFM plots
2017-03-02 removed inner pours on camera adapte board, re-panneled
2017-03-02 added PO for hat and adapter panel
2017-03-02 HOST pcb receipt
2017-03-02 Added Advanced circuits email receipt
2017-03-04 added new panel for PCB way
